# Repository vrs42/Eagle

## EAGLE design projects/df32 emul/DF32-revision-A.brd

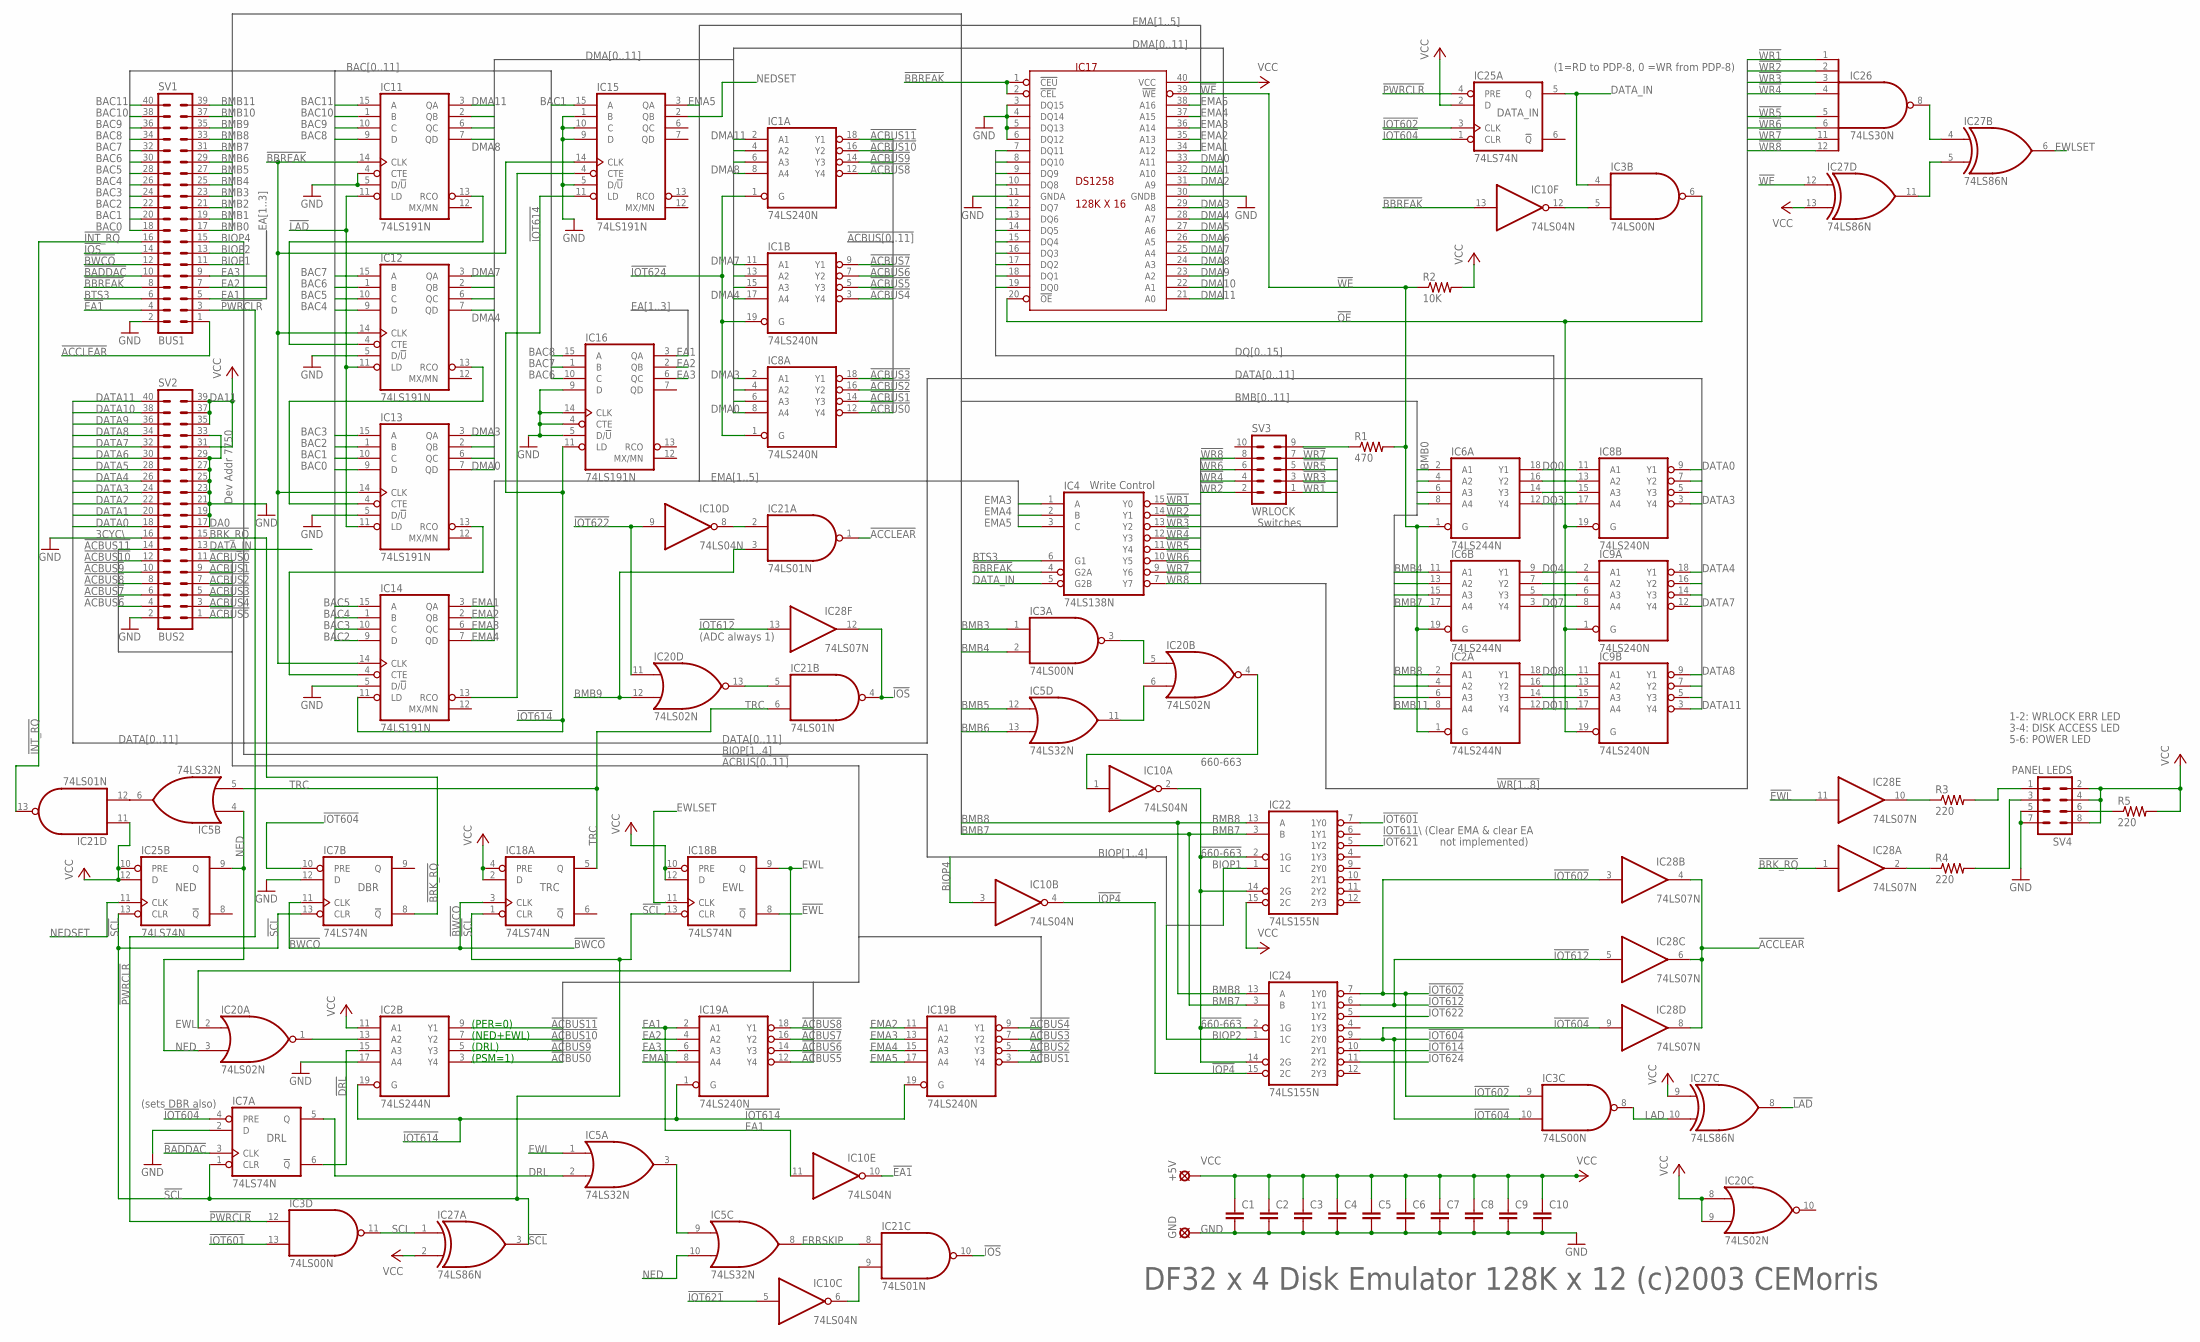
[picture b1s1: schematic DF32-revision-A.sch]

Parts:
+5V: SE14
C1, C2, C3, C4, C5, C6, C7, C8, C9, C10: C5/3.5; C5B3.5
GND: SE14
IC1, IC8, IC9, IC19: 74LS240N; DIL20
IC2, IC6: 74LS244N; DIL20
IC3: 74LS00N; DIL14
IC4: 74LS138N; DIL16
IC5: 74LS32N; DIL14
IC7, IC18, IC25: 74LS74N; DIL14
IC10: 74LS04N; DIL14
IC11, IC12, IC13, IC14, IC15, IC16: 74LS191N; DIL16
IC17: DS1258; DIL40
IC20: 74LS02N; DIL14
IC21: 74LS01N; DIL14
IC22, IC24: 74LS155N; DIL16
IC26: 74LS30N; DIL14
IC27: 74LS86N; DIL14
IC28: 74LS07N; DIL14
R1: 470; 0204/7
R2: 10K; 0204/7
R3, R4, R5: 220; 0204/5
SV1: BUS1; MA20-2
SV2: BUS2; MA20-2
SV3: WRLOCK; MA05-2
SV4: PANEL LEDS; MA04-2

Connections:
660-663: IC10.1 (I), IC20.4 (O)
!660-663: IC10.2 (O), IC22.2 (1G), IC22.14 (2G), IC24.2 (1G), IC24.14 (2G)
!(NED+EWL): IC2.13 (A2), IC20.1 (O)
!ACBUS0: IC2.3 (Y4), IC8.12 (Y4), SV2.11
!ACBUS1: IC8.14 (Y3), IC19.3 (Y4), SV2.9
!ACBUS2: IC8.16 (Y2), IC19.5 (Y3), SV2.7
!ACBUS3: IC8.18 (Y1), IC19.7 (Y2), SV2.5
!ACBUS4: IC1.3 (Y4), IC19.9 (Y1), SV2.3
!ACBUS5: IC1.5 (Y3), IC19.12 (Y4), SV2.1
!ACBUS6: IC1.7 (Y2), IC19.14 (Y3), SV2.4
!ACBUS7: IC1.9 (Y1), IC19.16 (Y2), SV2.6
!ACBUS8: IC1.12 (Y4), IC19.18 (Y1), SV2.8
!ACBUS9: IC1.14 (Y3), IC2.5 (Y3), SV2.10
!ACBUS10: IC1.16 (Y2), IC2.7 (Y2), SV2.12
!ACBUS11: IC1.18 (Y1), IC2.9 (Y1), SV2.14
!ACCLEAR: IC21.1 (O), IC28.4 (O), IC28.6 (O), IC28.8 (O), SV1.1
!BADDAC: IC7.3 (CLK), SV1.10
!BBREAK: IC4.4 (G2A), IC10.13 (I), IC11.14 (CLK), IC12.14 (CLK), IC13.14 (CLK), IC14.14 (CLK), IC15.14 (CLK), IC17.1 (!CEU), IC17.2 (!CEL), SV1.8
!BRK_RQ: IC7.8 (!Q), IC28.1 (I), SV2.15
!BWCO: IC7.11 (CLK), IC18.3 (CLK), SV1.12
!DRL: IC2.15 (A3), IC7.6 (!Q)
!EA1: IC10.10 (O), SV1.4
!EWL: IC18.8 (!Q), IC28.11 (I)
!INT_RQ: IC21.13 (O), SV1.16
!IOP4: IC10.4 (O), IC24.15 (2C)
!IOS: IC21.4 (O), IC21.10 (O), IC28.12 (O), SV1.14
!IOT601: IC3.13 (I1), IC22.7 (1Y0)
!IOT602: IC3.9 (I0), IC24.7 (1Y0), IC25.3 (CLK), IC28.3 (I)
!IOT604: IC3.10 (I1), IC7.4 (PRE), IC7.10 (PRE), IC24.9 (2Y0), IC25.1 (CLR), IC28.9 (I)
!IOT612: IC24.6 (1Y1), IC28.5 (I), IC28.13 (I)
!IOT614: IC2.19 (G), IC14.11 (LD), IC15.11 (LD), IC16.11 (LD), IC19.1 (G), IC19.19 (G), IC24.10 (2Y1)
!IOT621: IC10.5 (I), IC22.5 (1Y2)
!IOT622: IC10.9 (I), IC20.11 (I0), IC24.5 (1Y2)
!IOT624: IC1.1 (G), IC1.19 (G), IC8.1 (G), IC24.11 (2Y2)
!LAD: IC11.11 (LD), IC12.11 (LD), IC13.11 (LD), IC27.8 (O)
!OE: IC3.6 (O), IC8.19 (G), IC9.1 (G), IC9.19 (G), IC17.20 (!OE)
!PWRCLR: IC3.12 (I0), IC25.4 (PRE), SV1.3
!SCL: IC7.1 (CLR), IC7.13 (CLR), IC18.1 (CLR), IC18.13 (CLR), IC25.13 (CLR), IC27.3 (O)
!WE: IC2.1 (G), IC6.1 (G), IC6.19 (G), IC17.39 (!WE), IC27.12 (I0), R1.2, R2.1
!WR1: IC4.15 (Y0), IC26.1 (I0), SV3.1
!WR2: IC4.14 (Y1), IC26.2 (I1), SV3.2
!WR3: IC4.13 (Y2), IC26.3 (I2), SV3.3
!WR4: IC4.12 (Y3), IC26.4 (I3), SV3.4
!WR5: IC4.11 (Y4), IC26.5 (I4), SV3.5
!WR6: IC4.10 (Y5), IC26.6 (I5), SV3.6
!WR7: IC4.9 (Y6), IC26.11 (I6), SV3.7
!WR8: IC4.7 (Y7), IC26.12 (I7), SV3.8
BAC0: IC13.9 (D), SV1.18
BAC1: IC13.10 (C), IC15.15 (A), SV1.20
BAC2: IC13.1 (B), IC14.9 (D), SV1.22
BAC3: IC13.15 (A), IC14.10 (C), SV1.24
BAC4: IC12.9 (D), IC14.1 (B), SV1.26
BAC5: IC12.10 (C), IC14.15 (A), SV1.28
BAC6: IC12.1 (B), IC16.10 (C), SV1.30
BAC7: IC12.15 (A), IC16.1 (B), SV1.32
BAC8: IC11.9 (D), IC16.15 (A), SV1.34
BAC9: IC11.10 (C), SV1.36
BAC10: IC11.1 (B), SV1.38
BAC11: IC11.15 (A), SV1.40
BIOP1: IC22.1 (1C), SV1.11
BIOP2: IC24.1 (1C), SV1.13
BIOP4: IC10.3 (I), SV1.15
BMB0: IC6.2 (A1), SV1.17
BMB1: IC6.4 (A2), SV1.19
BMB2: IC6.6 (A3), SV1.21
BMB3: IC3.1 (I0), IC6.8 (A4), SV1.23
BMB4: IC3.2 (I1), IC6.11 (A1), SV1.25
BMB5: IC5.12 (I0), IC6.13 (A2), SV1.27
BMB6: IC5.13 (I1), IC6.15 (A3), SV1.29
BMB7: IC6.17 (A4), IC22.3 (B), IC24.3 (B), SV1.31
BMB8: IC2.2 (A1), IC22.13 (A), IC24.13 (A), SV1.33
BMB9: IC2.4 (A2), IC20.12 (I1), IC21.3 (I1), SV1.35
BMB10: IC2.6 (A3), SV1.37
BMB11: IC2.8 (A4), SV1.39
BTS3: IC4.6 (G1), SV1.6
DATA0: IC8.9 (Y1), SV2.18
DATA1: IC8.7 (Y2), SV2.20
DATA2: IC8.5 (Y3), SV2.22
DATA3: IC8.3 (Y4), SV2.24
DATA4: IC9.18 (Y1), SV2.26
DATA5: IC9.16 (Y2), SV2.28
DATA6: IC9.14 (Y3), SV2.30
DATA7: IC9.12 (Y4), SV2.32
DATA8: IC9.9 (Y1), SV2.34
DATA9: IC9.7 (Y2), SV2.36
DATA10: IC9.5 (Y3), SV2.38
DATA11: IC9.3 (Y4), SV2.40
DATA_IN: IC3.4 (I0), IC4.5 (G2B), IC25.5 (Q), SV2.13
DISK_LED: R4.2, SV4.3
DMA0: IC8.8 (A4), IC13.7 (QD), IC17.33 (A11)
DMA1: IC8.6 (A3), IC13.6 (QC), IC17.32 (A10)
DMA2: IC8.4 (A2), IC13.2 (QB), IC17.31 (A9)
DMA3: IC8.2 (A1), IC13.3 (QA), IC17.29 (A8)
DMA4: IC1.17 (A4), IC12.7 (QD), IC17.28 (A7)
DMA5: IC1.15 (A3), IC12.6 (QC), IC17.27 (A6)
DMA6: IC1.13 (A2), IC12.2 (QB), IC17.26 (A5)
DMA7: IC1.11 (A1), IC12.3 (QA), IC17.25 (A4)
DMA8: IC1.8 (A4), IC11.7 (QD), IC17.24 (A3)
DMA9: IC1.6 (A3), IC11.6 (QC), IC17.23 (A2)
DMA10: IC1.4 (A2), IC11.2 (QB), IC17.22 (A1)
DMA11: IC1.2 (A1), IC11.3 (QA), IC17.21 (A0)
DQ0: IC6.18 (Y1), IC8.11 (A1), IC17.19 (DQ0)
DQ1: IC6.16 (Y2), IC8.13 (A2), IC17.18 (DQ1)
DQ2: IC6.14 (Y3), IC8.15 (A3), IC17.17 (DQ2)
DQ3: IC6.12 (Y4), IC8.17 (A4), IC17.16 (DQ3)
DQ4: IC6.9 (Y1), IC9.2 (A1), IC17.15 (DQ4)
DQ5: IC6.7 (Y2), IC9.4 (A2), IC17.14 (DQ5)
DQ6: IC6.5 (Y3), IC9.6 (A3), IC17.13 (DQ6)
DQ7: IC6.3 (Y4), IC9.8 (A4), IC17.12 (DQ7)
DQ8: IC2.18 (Y1), IC9.11 (A1), IC17.10 (DQ8)
DQ9: IC2.16 (Y2), IC9.13 (A2), IC17.9 (DQ9)
DQ10: IC2.14 (Y3), IC9.15 (A3), IC17.8 (DQ10)
DQ11: IC2.12 (Y4), IC9.17 (A4), IC17.7 (DQ11)
DRL: IC5.2 (I1), IC7.5 (Q)
EA1: IC10.11 (I), IC16.3 (QA), IC19.2 (A1), SV1.5
EA2: IC16.2 (QB), IC19.4 (A2), SV1.7
EA3: IC16.6 (QC), IC19.6 (A3), SV1.9
EMA1: IC14.3 (QA), IC17.34 (A12), IC19.8 (A4)
EMA2: IC14.2 (QB), IC17.35 (A13), IC19.11 (A1)
EMA3: IC4.1 (A), IC14.6 (QC), IC17.36 (A14), IC19.13 (A2)
EMA4: IC4.2 (B), IC14.7 (QD), IC17.37 (A15), IC19.15 (A3)
EMA5: IC4.3 (C), IC15.3 (QA), IC17.38 (A16), IC19.17 (A4)
ERRSKIP: IC5.8 (O), IC21.8 (I0)
EWL: IC5.1 (I0), IC18.9 (Q), IC20.2 (I0)
EWLSET: IC18.11 (CLK), IC27.6 (O)
GND: C1.2, C2.2, C3.2, C4.2, C5.2, C6.2, C7.2, C8.2, C9.2, C10.2, GND.MP, IC1.10 (GND), IC2.10 (GND), IC2.17 (A4), IC3.7 (GND), IC4.8 (GND), IC5.7 (GND), IC6.10 (GND), IC7.2 (D), IC7.7 (GND), IC7.12 (D), IC8.10 (GND), IC9.10 (GND), IC10.7 (GND), IC11.4 (CTE), IC11.5 (D/!U), IC11.8 (GND), IC12.5 (D/!U), IC12.8 (GND), IC13.5 (D/!U), IC13.8 (GND), IC14.5 (D/!U), IC14.8 (GND), IC15.1 (B), IC15.5 (D/!U), IC15.8 (GND), IC15.9 (D), IC15.10 (C), IC16.4 (CTE), IC16.5 (D/!U), IC16.8 (GND), IC16.9 (D), IC16.14 (CLK), IC17.3 (DQ15), IC17.4 (DQ14), IC17.5 (DQ13), IC17.6 (DQ12), IC17.11 (GNDA), IC17.30 (GNDB), IC18.7 (GND), IC19.10 (GND), IC20.7 (GND), IC21.7 (GND), IC22.8 (GND), IC24.8 (GND), IC25.7 (GND), IC26.7 (GND), IC27.7 (GND), IC28.7 (GND), SV1.2, SV2.2, SV2.16, SV2.17, SV2.19, SV2.21, SV2.23, SV2.25, SV2.27, SV2.29, SV2.33, SV4.5, SV4.7
LAD: IC3.8 (O), IC27.10 (I1)
unnamed: IC27.5 (I1), IC27.11 (O)
unnamed: IC5.6 (O), IC21.12 (I1)
unnamed: IC28.10 (O), R3.1
unnamed: IC3.5 (I1), IC10.12 (O)
unnamed: IC28.2 (O), R4.1
unnamed: R5.1, SV4.6
unnamed: IC13.13 (RCO), IC14.4 (CTE)
unnamed: IC12.13 (RCO), IC13.4 (CTE)
unnamed: IC11.13 (RCO), IC12.4 (CTE)
unnamed: IC3.3 (O), IC20.5 (I0)
unnamed: IC14.13 (RCO), IC15.4 (CTE)
unnamed: IC5.11 (O), IC20.6 (I1)
unnamed: IC10.6 (O), IC21.9 (I1)
unnamed: IC20.13 (O), IC21.5 (I0)
unnamed: R1.1, SV3.9
unnamed: IC5.3 (O), IC5.9 (I0)
unnamed: IC10.8 (O), IC21.2 (I0)
unnamed: IC26.8 (O), IC27.4 (I0)
NED: IC5.4 (I0), IC5.10 (I1), IC20.3 (I1), IC25.9 (Q)
NEDSET: IC15.2 (QB), IC25.11 (CLK)
SCL: IC3.11 (O), IC27.1 (I0)
TRC: IC5.5 (I1), IC18.5 (Q), IC21.6 (I1)
VCC: +5V.MP, C1.1, C2.1, C3.1, C4.1, C5.1, C6.1, C7.1, C8.1, C9.1, C10.1, IC1.20 (VCC), IC2.11 (A1), IC2.20 (VCC), IC3.14 (VCC), IC4.16 (VCC), IC5.14 (VCC), IC6.20 (VCC), IC7.14 (VCC), IC8.20 (VCC), IC9.20 (VCC), IC10.14 (VCC), IC11.16 (VCC), IC12.16 (VCC), IC13.16 (VCC), IC14.16 (VCC), IC15.16 (VCC), IC16.16 (VCC), IC17.40 (VCC), IC18.2 (D), IC18.4 (PRE), IC18.10 (PRE), IC18.12 (D), IC18.14 (VCC), IC19.20 (VCC), IC20.8 (I0), IC20.9 (I1), IC20.14 (VCC), IC21.11 (I0), IC21.14 (VCC), IC22.15 (2C), IC22.16 (VCC), IC24.16 (VCC), IC25.2 (D), IC25.10 (PRE), IC25.12 (D), IC25.14 (VCC), IC26.14 (VCC), IC27.2 (I1), IC27.9 (I0), IC27.13 (I1), IC27.14 (VCC), IC28.14 (VCC), R2.2, R5.2, SV2.31, SV2.35, SV2.37, SV2.39, SV4.2, SV4.4, SV4.8
WRITELOCK_LED: R3.2, SV4.1

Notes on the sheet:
(PER=0)
DF32 x 4 Disk Emulator 128K x 12 (c)2003 CEMorris
NED
DBR
TRC
EWL
IOT611\\ (Clear EMA & clear EA
not implemented)
(1=RD to PDP-8, 0 =WR from PDP-8)
DRL
(sets DBR also)
Dev Addr 7750
DA11
DA0
3CYC\\
DATA_IN
(PSM=1)
(NED+EWL)
(DRL)
(ADC always 1)
Write Control
Switches
1-2: WRLOCK ERR LED
3-4: DISK ACCESS LED
5-6: POWER LED

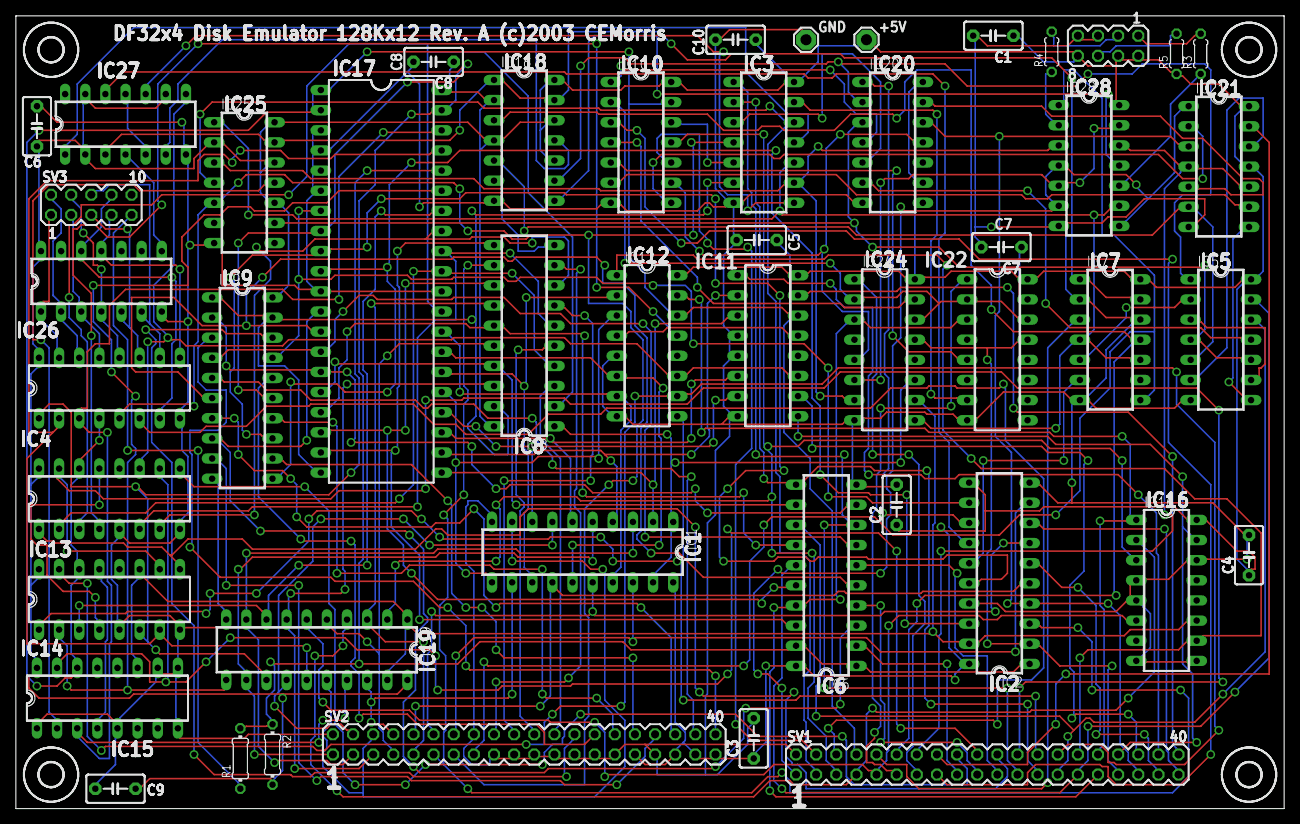
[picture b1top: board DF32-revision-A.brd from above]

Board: 2 copper layers, 160.0 x 100.0 mm, 52 parts (0 on the bottom side), 151 nets.

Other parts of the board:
U$1, U$2, U$3, U$4: 3,0

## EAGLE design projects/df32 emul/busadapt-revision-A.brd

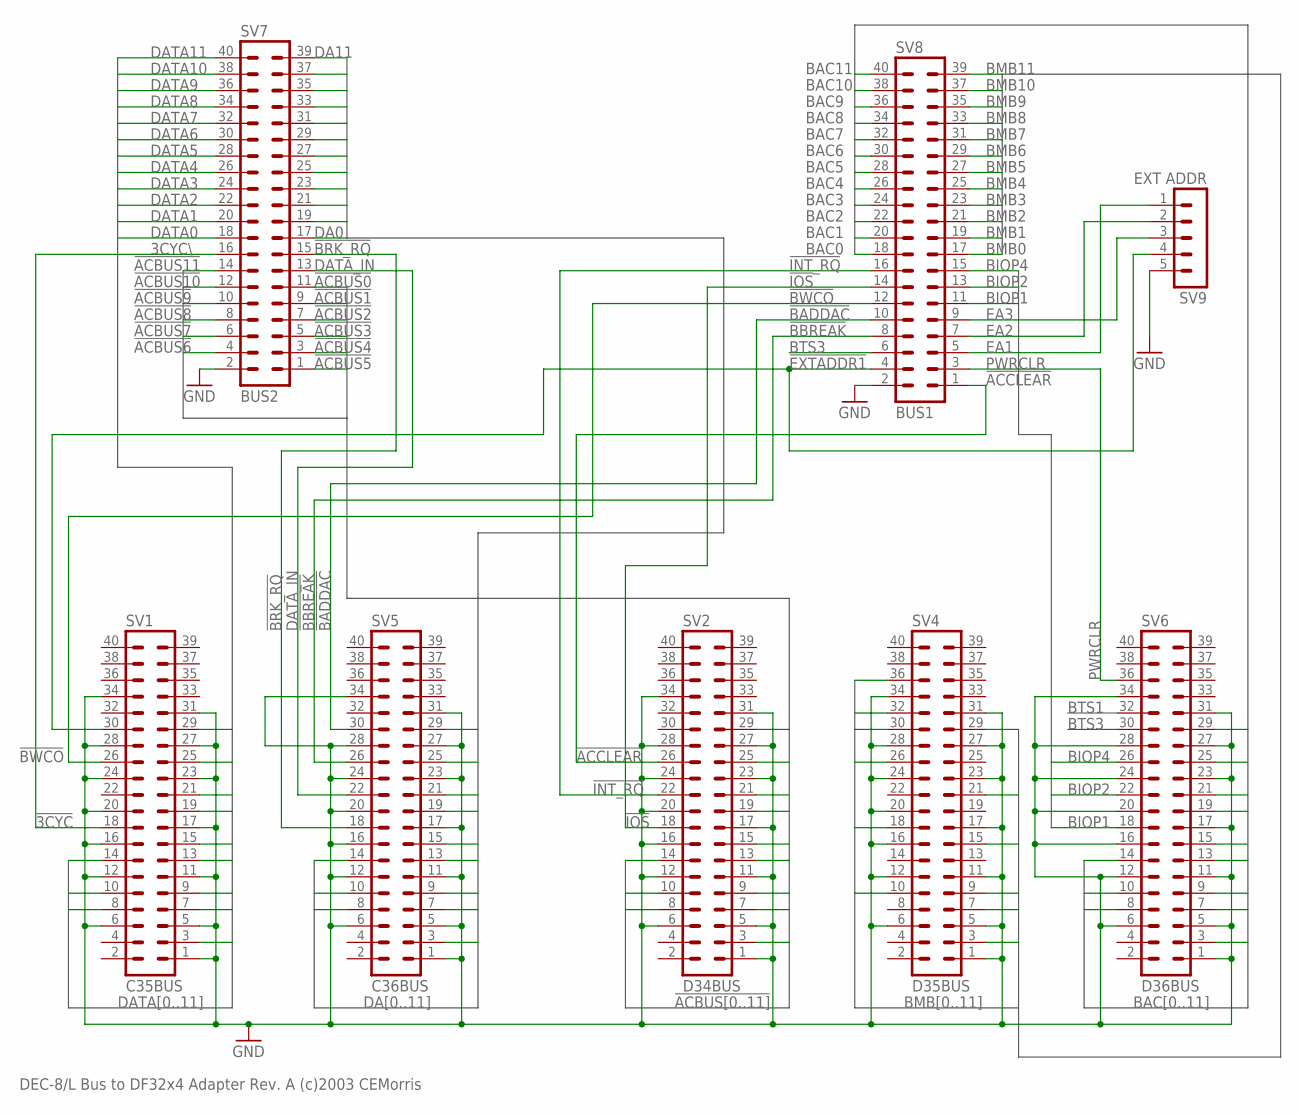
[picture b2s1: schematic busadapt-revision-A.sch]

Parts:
SV1: C35BUS; MA20-2
SV2: D34BUS; MA20-2
SV4: D35BUS; MA20-2
SV5: C36BUS; MA20-2
SV6: D36BUS; MA20-2
SV7: BUS2; MA20-2
SV8: BUS1; MA20-2
SV9: EXT ADDR; MA05-1

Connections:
!3CYC: SV1.18, SV7.16
!ACBUS0: SV2.3, SV7.11
!ACBUS1: SV2.7, SV7.9
!ACBUS2: SV2.9, SV7.7
!ACBUS3: SV2.13, SV7.5
!ACBUS4: SV2.15, SV7.3
!ACBUS5: SV2.19, SV7.1
!ACBUS6: SV2.21, SV7.4
!ACBUS7: SV2.25, SV7.6
!ACBUS8: SV2.29, SV7.8
!ACBUS9: SV2.8, SV7.10
!ACBUS10: SV2.10, SV7.12
!ACBUS11: SV2.14, SV7.14
!ACCLEAR: SV2.26, SV8.1
!BADDAC: SV5.30, SV8.10
!BBREAK: SV5.26, SV8.8
!BRK_RQ: SV5.18, SV7.15
!BWCO: SV1.26, SV8.12
!EXTADDR1: SV1.30, SV8.4, SV9.4
!INT_RQ: SV2.22, SV8.16
!IOS: SV2.18, SV8.14
BAC0: SV6.3, SV8.18
BAC1: SV6.7, SV8.20
BAC2: SV6.9, SV8.22
BAC3: SV6.13, SV8.24
BAC4: SV6.15, SV8.26
BAC5: SV6.19, SV8.28
BAC6: SV6.21, SV8.30
BAC7: SV6.25, SV8.32
BAC8: SV6.29, SV8.34
BAC9: SV6.8, SV8.36
BAC10: SV6.10, SV8.38
BAC11: SV6.14, SV8.40
BIOP1: SV6.18, SV8.11
BIOP2: SV6.22, SV8.13
BIOP4: SV6.26, SV8.15
BMB0: SV4.3, SV8.17
BMB1: SV4.7, SV8.19
BMB2: SV4.9, SV8.21
BMB3: SV4.15, SV8.23
BMB4: SV4.21, SV8.25
BMB5: SV4.29, SV8.27
BMB6: SV4.10, SV8.29
BMB7: SV4.18, SV8.31
BMB8: SV4.26, SV8.33
BMB9: SV4.30, SV8.35
BMB10: SV4.32, SV8.37
BMB11: SV4.36, SV8.39
BTS3: SV6.30, SV8.6
DA0: SV5.3, SV7.17
DA1: SV5.7, SV7.19
DA2: SV5.9, SV7.21
DA3: SV5.13, SV7.23
DA4: SV5.15, SV7.25
DA5: SV5.19, SV7.27
DA6: SV5.21, SV7.29
DA7: SV5.25, SV7.31
DA8: SV5.29, SV7.33
DA9: SV5.8, SV7.35
DA10: SV5.10, SV7.37
DA11: SV5.14, SV7.39
DATA0: SV1.3, SV7.18
DATA1: SV1.7, SV7.20
DATA2: SV1.9, SV7.22
DATA3: SV1.13, SV7.24
DATA4: SV1.15, SV7.26
DATA5: SV1.19, SV7.28
DATA6: SV1.21, SV7.30
DATA7: SV1.25, SV7.32
DATA8: SV1.29, SV7.34
DATA9: SV1.8, SV7.36
DATA10: SV1.10, SV7.38
DATA11: SV1.14, SV7.40
DATA_IN: SV5.22, SV7.13
EA1: SV8.5, SV9.1
EA2: SV8.7, SV9.2
EA3: SV8.9, SV9.3
GND: SV1.1, SV1.5, SV1.6, SV1.11, SV1.12, SV1.16, SV1.17, SV1.20, SV1.23, SV1.24, SV1.27, SV1.28, SV1.31, SV1.34, SV2.1, SV2.5, SV2.6, SV2.11, SV2.12, SV2.16, SV2.17, SV2.20, SV2.23, SV2.24, SV2.27, SV2.28, SV2.31, SV2.34, SV4.1, SV4.5, SV4.6, SV4.11, SV4.12, SV4.16, SV4.17, SV4.20, SV4.23, SV4.24, SV4.27, SV4.28, SV4.31, SV4.34, SV5.1, SV5.5, SV5.6, SV5.11, SV5.12, SV5.16, SV5.17, SV5.20, SV5.23, SV5.24, SV5.27, SV5.28, SV5.31, SV5.34, SV6.1, SV6.5, SV6.6, SV6.11, SV6.12, SV6.16, SV6.17, SV6.20, SV6.23, SV6.24, SV6.27, SV6.28, SV6.31, SV6.34, SV7.2, SV8.2, SV9.5
PWRCLR: SV6.36, SV8.3

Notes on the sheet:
DEC-8/L Bus to DF32x4 Adapter Rev. A (c)2003 CEMorris
DA11
DA0
3CYC\\
BTS1

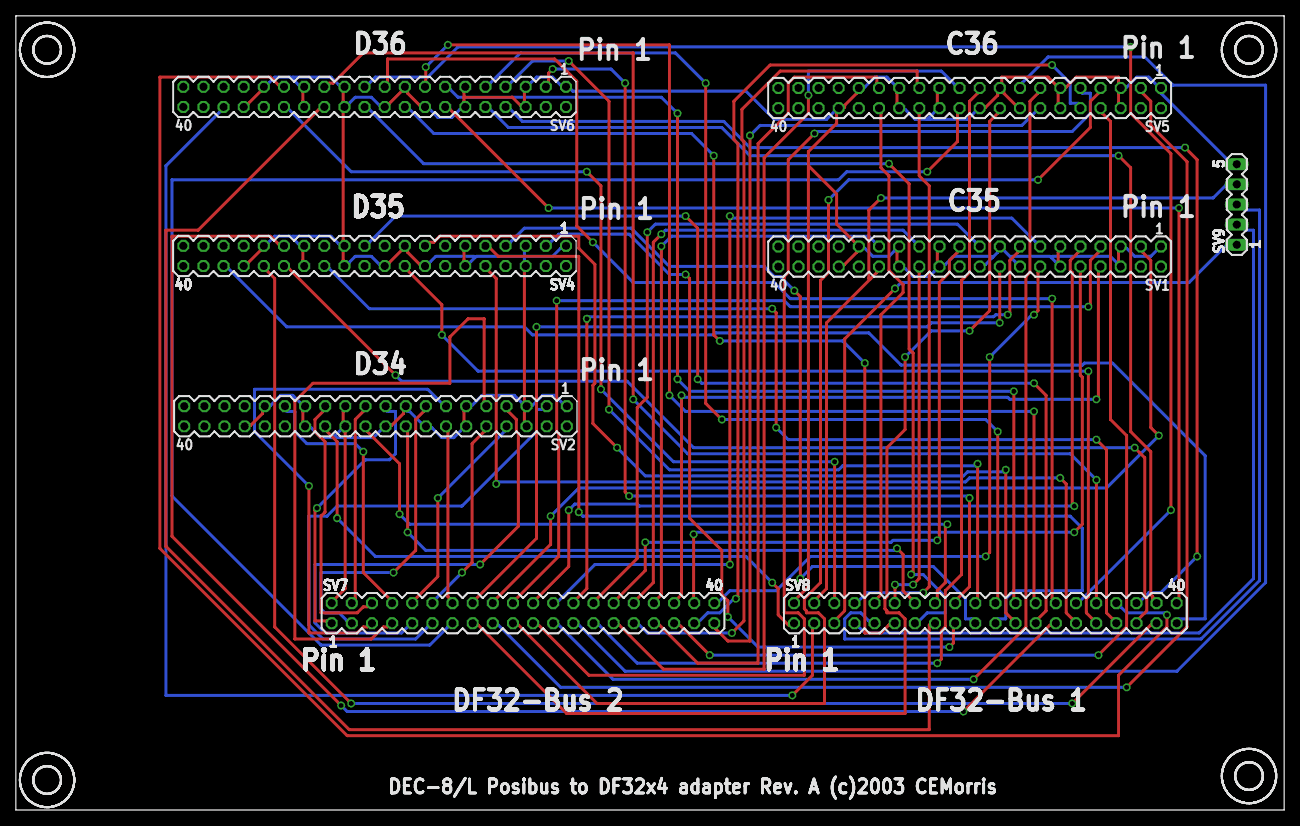
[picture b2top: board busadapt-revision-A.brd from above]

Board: 2 copper layers, 159.9 x 100.2 mm, 12 parts (0 on the bottom side), 79 nets.

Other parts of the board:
U$1, U$2, U$3, U$4: 3,3

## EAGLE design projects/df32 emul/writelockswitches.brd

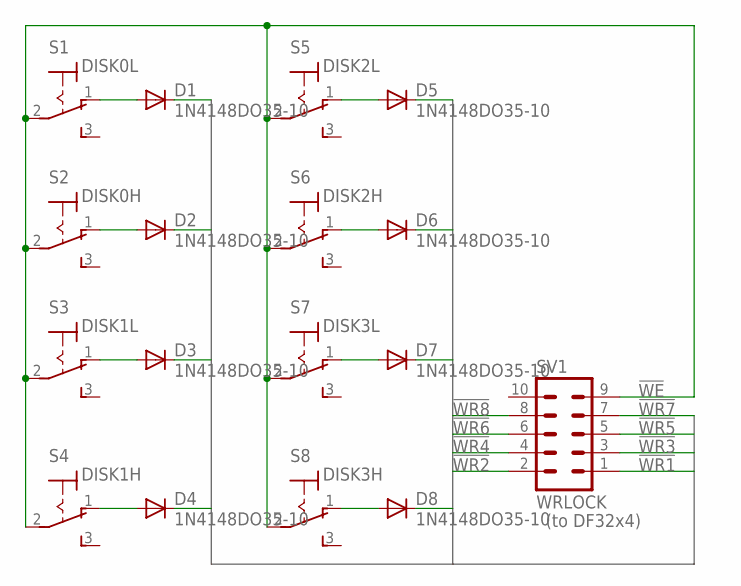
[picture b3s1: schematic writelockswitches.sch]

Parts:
D1, D2, D3, D4, D5, D6, D7, D8: 1N4148DO35-10; DO35-10
S1: DISK0L; 320-916
S2: DISK0H; 320-916
S3: DISK1L; 320-916
S4: DISK1H; 320-916
S5: DISK2L; 320-916
S6: DISK2H; 320-916
S7: DISK3L; 320-916
S8: DISK3H; 320-916
SV1: WRLOCK; MA05-2

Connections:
!WE: S1.2, S2.2, S3.2, S4.2, S5.2, S6.2, S7.2, S8.2, SV1.9
!WR1: D1.C, SV1.1
!WR2: D2.C, SV1.2
!WR3: D3.C, SV1.3
!WR4: D4.C, SV1.4
!WR5: D5.C, SV1.5
!WR6: D6.C, SV1.6
!WR7: D7.C, SV1.7
!WR8: D8.C, SV1.8
unnamed: D1.A, S1.1 (O)
unnamed: D2.A, S2.1 (O)
unnamed: D3.A, S3.1 (O)
unnamed: D4.A, S4.1 (O)
unnamed: D5.A, S5.1 (O)
unnamed: D6.A, S6.1 (O)
unnamed: D7.A, S7.1 (O)
unnamed: D8.A, S8.1 (O)

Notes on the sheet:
(to DF32x4)

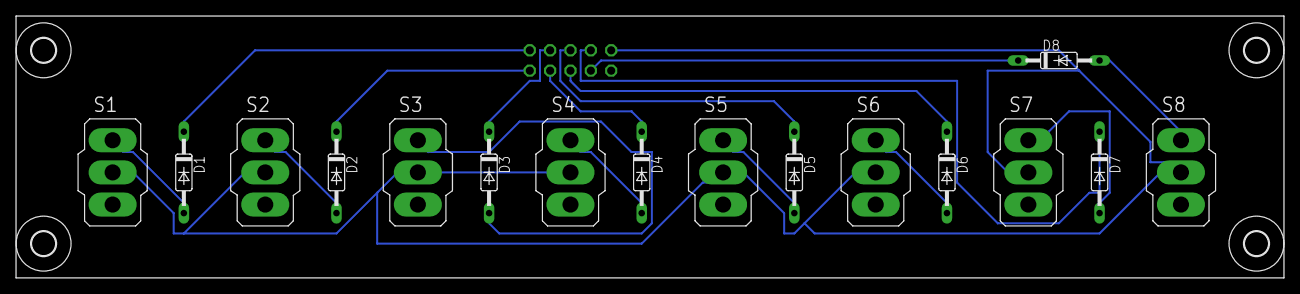
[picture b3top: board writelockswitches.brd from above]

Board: 1 copper layer, 158.3 x 32.7 mm, 21 parts (1 on the bottom side), 17 nets.

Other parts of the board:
U$1, U$2, U$3, U$4: 3,0

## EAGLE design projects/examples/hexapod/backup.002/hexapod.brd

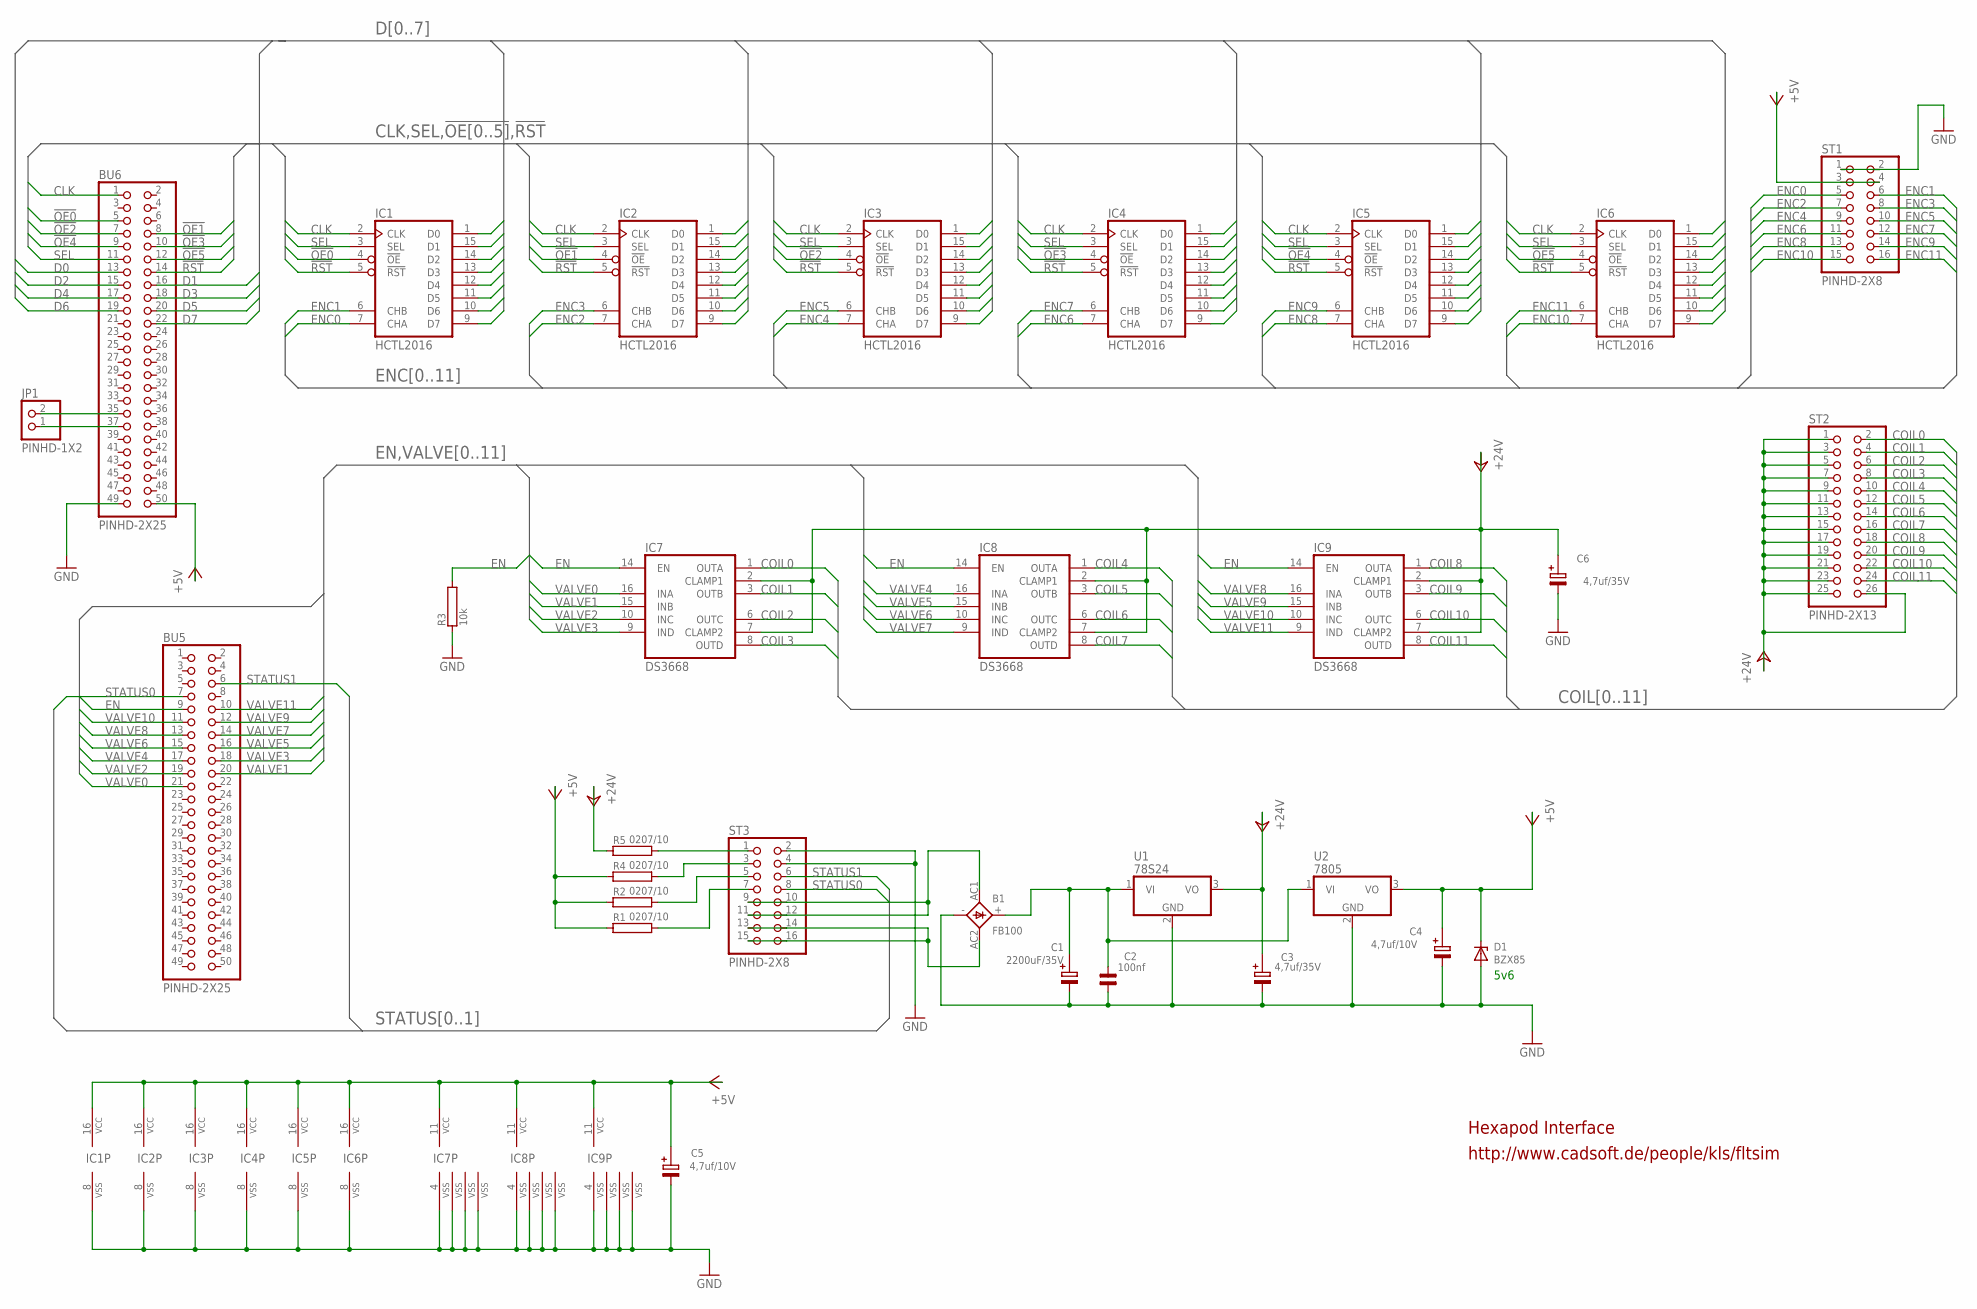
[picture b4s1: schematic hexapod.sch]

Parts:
B1: FB100
BU5, BU6: PINHD-2X25; 2X25
C1: 2200uF/35V; E35-16
C2: 100nf; C5B2,5A
C3, C6: 4,7uf/35V; E2,5-5
C4, C5: 4,7uf/10V; E2,5-5
D1: BZX85; DO41Z10
IC1, IC2, IC3, IC4, IC5, IC6: HCTL2016; DIL-16
IC7, IC8, IC9: DS3668; DIL-16
JP1: PINHD-1X2; 1X02
R1, R2, R4, R5: 0207/10
R3: 10k; 0207/10@1
ST1, ST3: PINHD-2X8; ML16
ST2: PINHD-2X13; ML26
U1: 78S24; TO220H
U2: 7805; TO220H

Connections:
!OE0: BU6.5, IC1.4 (!OE)
!OE1: BU6.8, IC2.4 (!OE)
!OE2: BU6.7, IC3.4 (!OE)
!OE3: BU6.10, IC4.4 (!OE)
!OE4: BU6.9, IC5.4 (!OE)
!OE5: BU6.12, IC6.4 (!OE)
!RST: BU6.14, IC1.5 (!RST), IC2.5 (!RST), IC3.5 (!RST), IC4.5 (!RST), IC5.5 (!RST), IC6.5 (!RST)
+5V: BU6.50, C4.+, C5.+, D1.C, IC1.16 (VCC), IC2.16 (VCC), IC3.16 (VCC), IC4.16 (VCC), IC5.16 (VCC), IC6.16 (VCC), IC7.11 (VCC), IC8.11 (VCC), IC9.11 (VCC), R1.1, R2.1, R4.1, ST1.3, ST1.4, U2.3 (VO)
+24V: C3.+, C6.+, IC7.2 (CLAMP1), IC7.7 (CLAMP2), IC8.2 (CLAMP1), IC8.7 (CLAMP2), IC9.2 (CLAMP1), IC9.7 (CLAMP2), R5.1, ST2.1, ST2.3, ST2.5, ST2.7, ST2.9, ST2.11, ST2.13, ST2.15, ST2.17, ST2.19, ST2.21, ST2.23, ST2.25, ST2.26, U1.3 (VO)
AC1: B1.AC1, ST3.9, ST3.10, ST3.11, ST3.12
AC2: B1.AC2, ST3.13, ST3.14, ST3.15, ST3.16
CLK: BU6.1, IC1.2 (CLK), IC2.2 (CLK), IC3.2 (CLK), IC4.2 (CLK), IC5.2 (CLK), IC6.2 (CLK)
COIL0: IC7.1 (OUTA), ST2.2
COIL1: IC7.3 (OUTB), ST2.4
COIL2: IC7.6 (OUTC), ST2.6
COIL3: IC7.8 (OUTD), ST2.8
COIL4: IC8.1 (OUTA), ST2.10
COIL5: IC8.3 (OUTB), ST2.12
COIL6: IC8.6 (OUTC), ST2.14
COIL7: IC8.8 (OUTD), ST2.16
COIL8: IC9.1 (OUTA), ST2.18
COIL9: IC9.3 (OUTB), ST2.20
COIL10: IC9.6 (OUTC), ST2.22
COIL11: IC9.8 (OUTD), ST2.24
D0: BU6.13, IC1.1 (D0), IC2.1 (D0), IC3.1 (D0), IC4.1 (D0), IC5.1 (D0), IC6.1 (D0)
D1: BU6.16, IC1.15 (D1), IC2.15 (D1), IC3.15 (D1), IC4.15 (D1), IC5.15 (D1), IC6.15 (D1)
D2: BU6.15, IC1.14 (D2), IC2.14 (D2), IC3.14 (D2), IC4.14 (D2), IC5.14 (D2), IC6.14 (D2)
D3: BU6.18, IC1.13 (D3), IC2.13 (D3), IC3.13 (D3), IC4.13 (D3), IC5.13 (D3), IC6.13 (D3)
D4: BU6.17, IC1.12 (D4), IC2.12 (D4), IC3.12 (D4), IC4.12 (D4), IC5.12 (D4), IC6.12 (D4)
D5: BU6.20, IC1.11 (D5), IC2.11 (D5), IC3.11 (D5), IC4.11 (D5), IC5.11 (D5), IC6.11 (D5)
D6: BU6.19, IC1.10 (D6), IC2.10 (D6), IC3.10 (D6), IC4.10 (D6), IC5.10 (D6), IC6.10 (D6)
D7: BU6.22, IC1.9 (D7), IC2.9 (D7), IC3.9 (D7), IC4.9 (D7), IC5.9 (D7), IC6.9 (D7)
EN: BU5.9, IC7.14 (EN), IC8.14 (EN), IC9.14 (EN), R3.2
ENC0: IC1.7 (CHA), ST1.5
ENC1: IC1.6 (CHB), ST1.6
ENC2: IC2.7 (CHA), ST1.7
ENC3: IC2.6 (CHB), ST1.8
ENC4: IC3.7 (CHA), ST1.9
ENC5: IC3.6 (CHB), ST1.10
ENC6: IC4.7 (CHA), ST1.11
ENC7: IC4.6 (CHB), ST1.12
ENC8: IC5.7 (CHA), ST1.13
ENC9: IC5.6 (CHB), ST1.14
ENC10: IC6.7 (CHA), ST1.15
ENC11: IC6.6 (CHB), ST1.16
GND: B1.-, BU6.49, C1.-, C2.1, C3.-, C4.-, C5.-, C6.-, D1.A, IC1.8 (VSS), IC2.8 (VSS), IC3.8 (VSS), IC4.8 (VSS), IC5.8 (VSS), IC6.8 (VSS), IC7.4 (VSS), IC7.5 (VSS), IC7.12 (VSS), IC7.13 (VSS), IC8.4 (VSS), IC8.5 (VSS), IC8.12 (VSS), IC8.13 (VSS), IC9.4 (VSS), IC9.5 (VSS), IC9.12 (VSS), IC9.13 (VSS), R3.1, ST1.1, ST1.2, ST3.2, ST3.4, U1.2 (GND), U2.2 (GND)
unnamed: R5.2, ST3.1
unnamed: R4.2, ST3.3
unnamed: R2.2, ST3.5
unnamed: R1.2, ST3.7
unnamed: BU6.35, JP1.2
unnamed: BU6.37, JP1.1
SEL: BU6.11, IC1.3 (SEL), IC2.3 (SEL), IC3.3 (SEL), IC4.3 (SEL), IC5.3 (SEL), IC6.3 (SEL)
STATUS0: BU5.7, ST3.8
STATUS1: BU5.6, ST3.6
VALVE0: BU5.21, IC7.16 (INA)
VALVE1: BU5.20, IC7.15 (INB)
VALVE2: BU5.19, IC7.10 (INC)
VALVE3: BU5.18, IC7.9 (IND)
VALVE4: BU5.17, IC8.16 (INA)
VALVE5: BU5.16, IC8.15 (INB)
VALVE6: BU5.15, IC8.10 (INC)
VALVE7: BU5.14, IC8.9 (IND)
VALVE8: BU5.13, IC9.16 (INA)
VALVE9: BU5.12, IC9.15 (INB)
VALVE10: BU5.11, IC9.10 (INC)
VALVE11: BU5.10, IC9.9 (IND)
VIN: B1.+, C1.+, C2.2, U1.1 (VI), U2.1 (VI)

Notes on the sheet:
Hexapod Interface
5v6
http://www.cadsoft.de/people/kls/fltsim

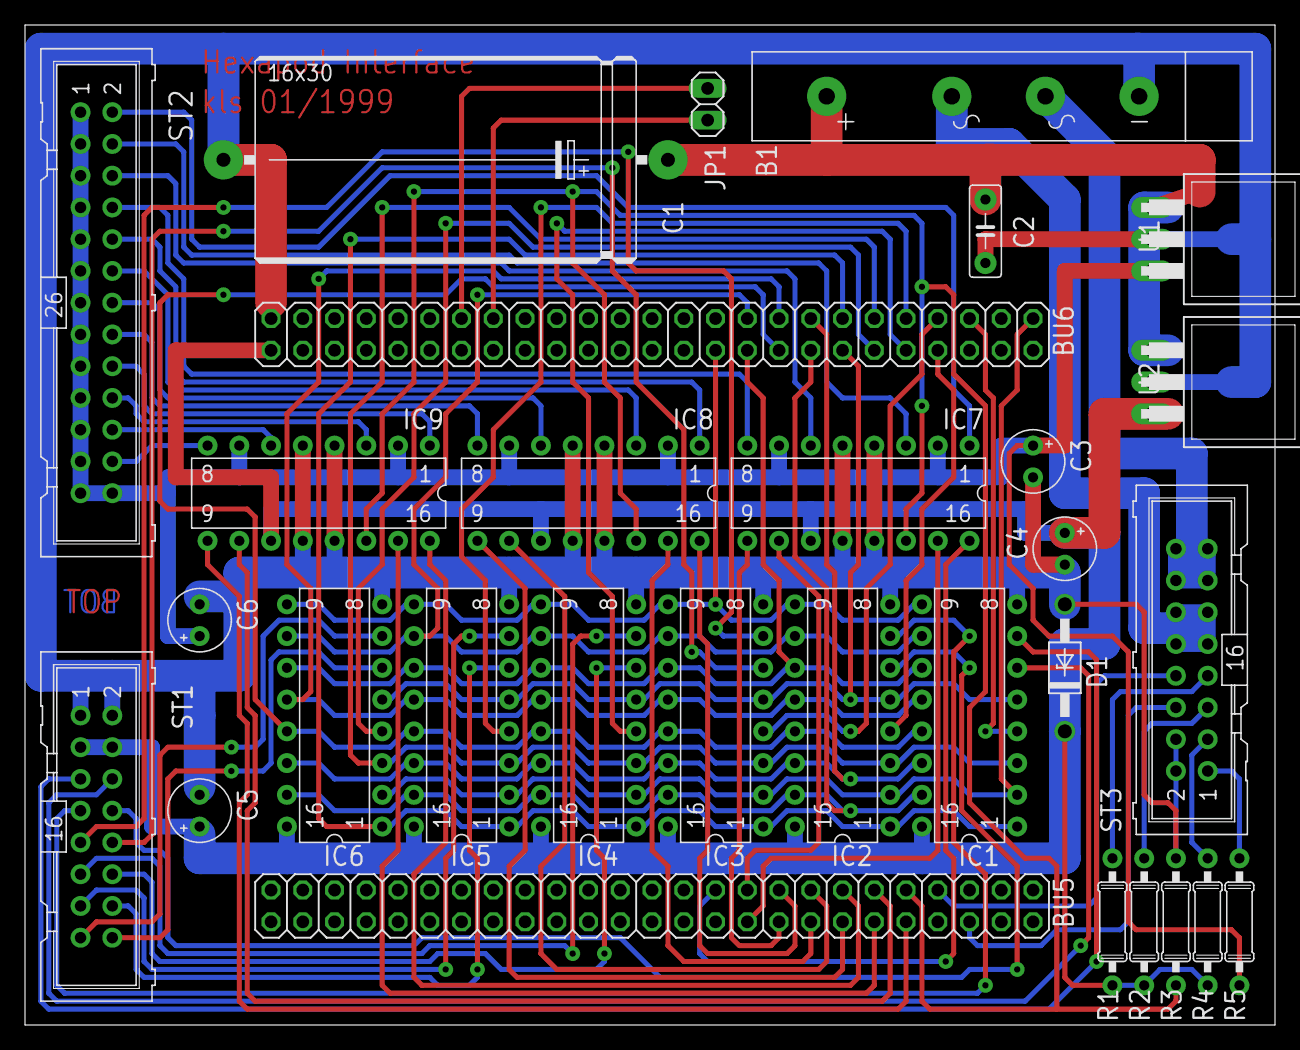
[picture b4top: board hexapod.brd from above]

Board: 2 copper layers, 100.0 x 80.0 mm, 30 parts (0 on the bottom side), 68 nets.

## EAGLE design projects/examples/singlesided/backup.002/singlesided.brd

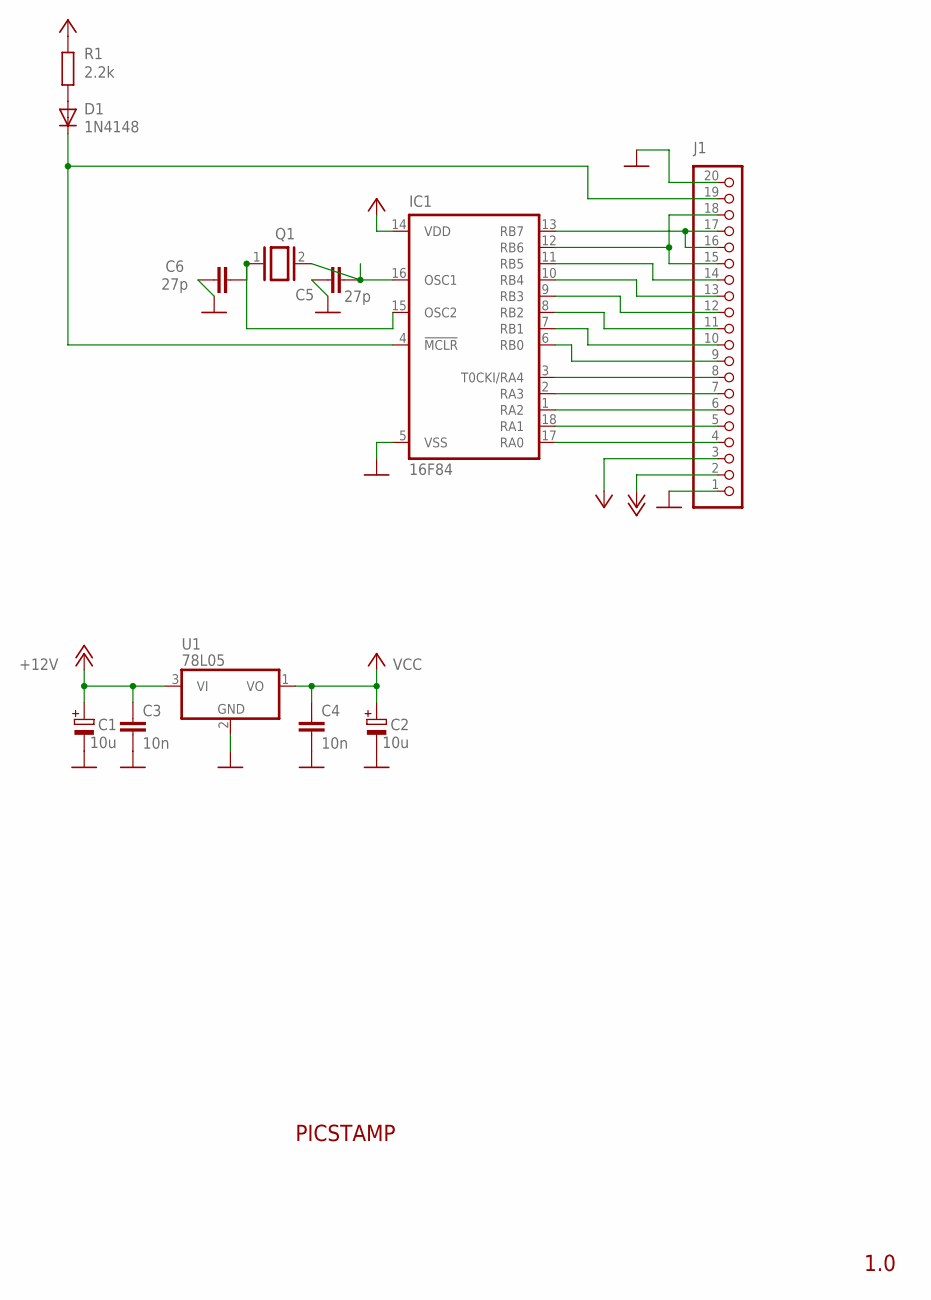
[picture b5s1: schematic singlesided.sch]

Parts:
C1, C2: 10u; E2,5-6
C3, C4: 10n; C025-025X050
C5, C6: 27p; C2.5-2
D1: 1N4148; DO35-10
IC1: 16F84; DIL18
J1: PINHD-1X20; 1X20
Q1: XTAL/S; QS
R1: 2.2k; 0207/10
U1: 78L05; TO92

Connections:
+12V: C1.+, C3.1, J1.2, U1.3 (VI)
A0: IC1.17 (RA0), J1.4
A1: IC1.18 (RA1), J1.5
A2: IC1.1 (RA2), J1.6
A3: IC1.2 (RA3), J1.7
A4: IC1.3 (T0CKI/RA4), J1.8
B0: IC1.6 (RB0), J1.9
B1: IC1.7 (RB1), J1.10
B2: IC1.8 (RB2), J1.11
B3: IC1.9 (RB3), J1.12
B4: IC1.10 (RB4), J1.13
B5: IC1.11 (RB5), J1.14
B6: IC1.12 (RB6), J1.15, J1.18
B7: IC1.13 (RB7), J1.16, J1.17
GND: C1.-, C2.-, C3.2, C4.2, C5.1, C6.1, IC1.5 (VSS), J1.1, J1.20, U1.2 (GND)
unnamed: D1.K (C), IC1.4 (!MCLR), J1.19
unnamed: D1.A, R1.1
unnamed: C5.2, IC1.16 (OSC1), Q1.2
unnamed: C6.2, IC1.15 (OSC2), Q1.1
VCC: C2.+, C4.1, IC1.14 (VDD), J1.3, R1.2, U1.1 (VO)

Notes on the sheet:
PICSTAMP
1.0

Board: 2 copper layers, 12 parts (0 on the bottom side), 20 nets, no tracks yet.

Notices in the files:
projects/df32 emul/DF32-revision-A.brd:
DF32x4 Disk Emulator 128Kx12 Rev. A (c)2003 CEMorris
